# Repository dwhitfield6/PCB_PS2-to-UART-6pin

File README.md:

# PCB_PS2-to-UART-6pin
PS2 to UART PCB for use with 6 pin usb to ttl. Arduino shield for PS_2 keyboard. Uses pic16f1705 to convert PS/2
scan codes to TTL UART Ascii characters.

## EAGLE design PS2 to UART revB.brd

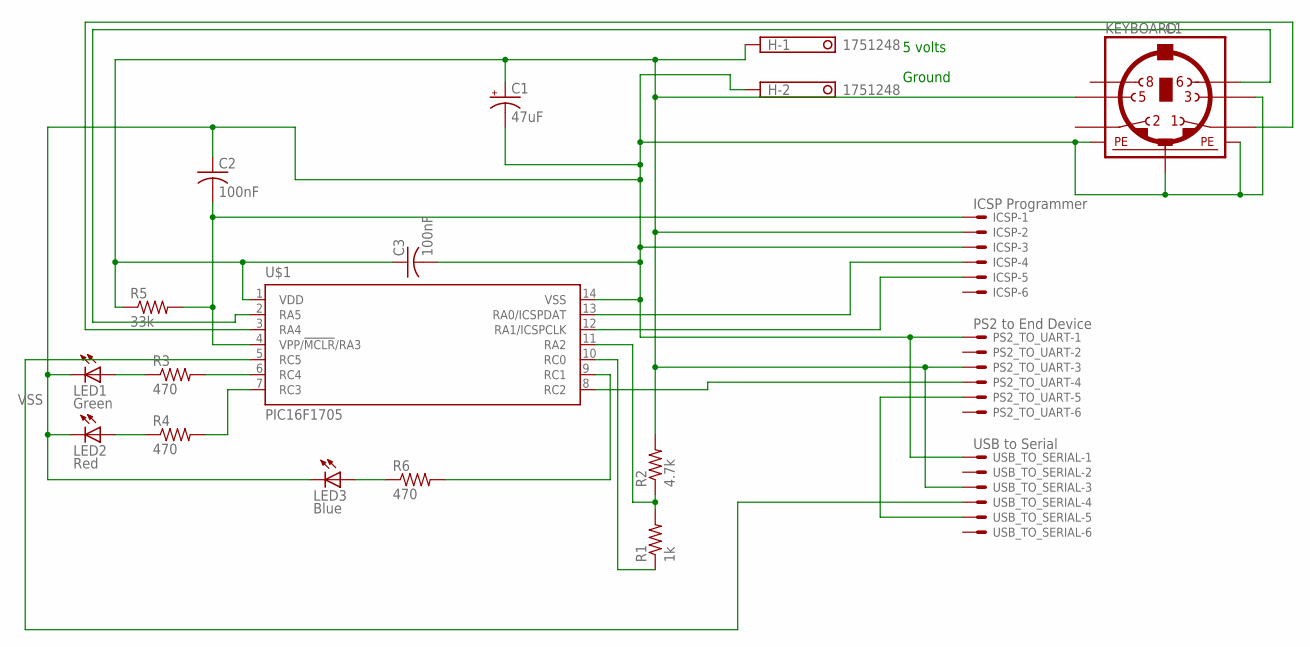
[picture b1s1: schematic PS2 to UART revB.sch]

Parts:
C1: 47uF; E2,5-7
C2, C3: 100nF; C025-030X050
H: 1751248
ICSP: ICSP Programmer; 22-23-2061
KEYBOARD: C1; M_DIN6
LED1: Green; LED5MM
LED2: Red; LED5MM
LED3: Blue; LED5MM
PS2_TO_UART: PS2 to End Device; 22-23-2061
R1: 1k; 0207/10
R2: 4.7k; 0207/10
R3, R4, R6: 470; 0207/10
R5: 33k; 0207/12
U$1: PIC16F1705; SO-14
USB_TO_SERIAL: USB to Serial; 22-23-2061

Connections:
unnamed: R1.2, R2.1, U$1.11 (RA2)
unnamed: R1.1, U$1.10 (RC0)
unnamed: R3.2, U$1.6 (RC4)
unnamed: R4.2, U$1.7 (RC3)
unnamed: LED1.A, R3.1
unnamed: LED2.A, R4.1
unnamed: U$1.5 (RC5), USB_TO_SERIAL.4
unnamed: PS2_TO_UART.4, U$1.8 (RC2)
unnamed: C2.2, ICSP.1, R5.2, U$1.4 (VPP/!MCLR!/RA3)
unnamed: ICSP.4, U$1.13 (RA0/ICSPDAT)
unnamed: ICSP.5, U$1.12 (RA1/ICSPCLK)
unnamed: PS2_TO_UART.5, USB_TO_SERIAL.5
unnamed: LED3.A, R6.1
unnamed: R6.2, U$1.9 (RC1)
unnamed: KEYBOARD.1, U$1.3 (RA4)
unnamed: KEYBOARD.6, U$1.2 (RA5)
VDD: C1.+, C3.1, H.1, ICSP.2, KEYBOARD.5, PS2_TO_UART.3, R2.2, R5.1, U$1.1 (VDD), USB_TO_SERIAL.3
VSS: C1.-, C2.1, C3.2, H.2, ICSP.3, KEYBOARD.3, KEYBOARD.SH1 (PE1), KEYBOARD.SH2 (PE2), KEYBOARD.SH3 (PE3), LED1.K (C), LED2.K (C), LED3.K (C), PS2_TO_UART.1, U$1.14 (VSS), USB_TO_SERIAL.1

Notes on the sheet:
Ground
5 volts

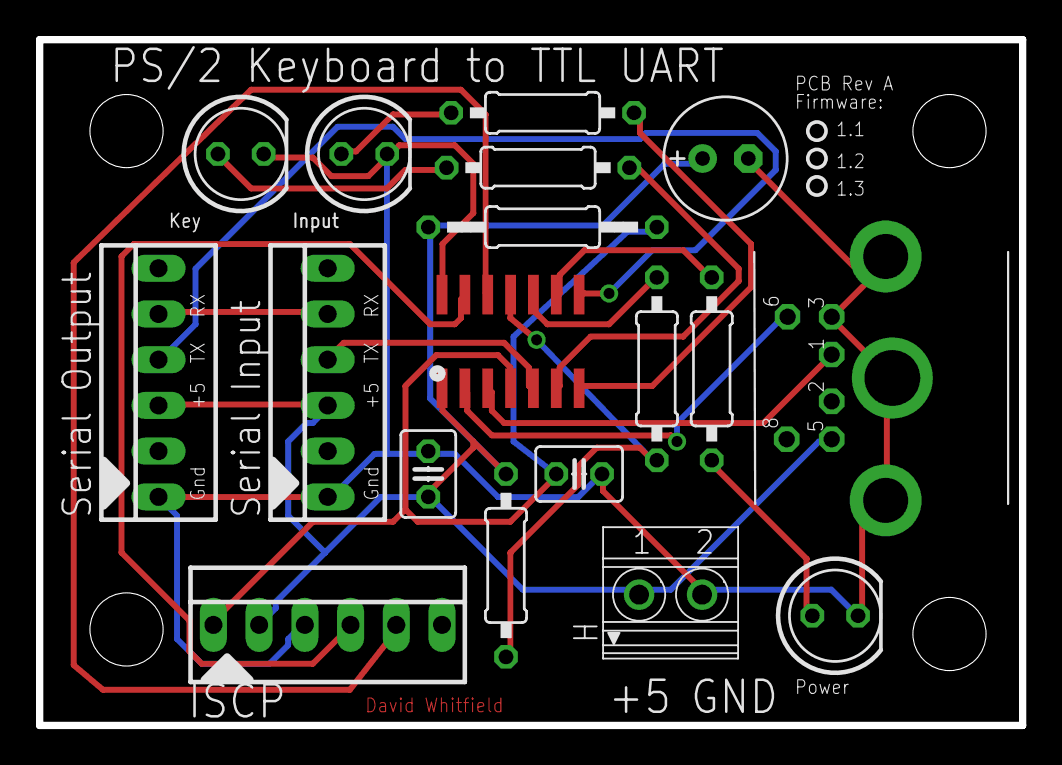
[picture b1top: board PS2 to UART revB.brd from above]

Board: 2 copper layers, 54.6 x 38.1 mm, 18 parts (0 on the bottom side), 18 nets.

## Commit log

2015-01-28 :boom::camel: Added .gitattributes & .gitignore files
2015-01-28 Create
    - Created
